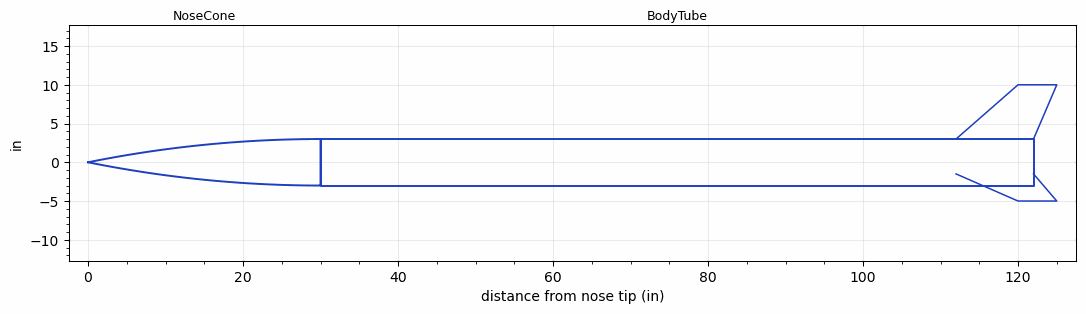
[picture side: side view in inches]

<RASAeroDocument>
 <FileVersion>2</FileVersion>
 <RocketDesign>
  <NoseCone>
   <Length>30</Length>
   <Diameter>6</Diameter>
   <Shape>Tangent Ogive</Shape>
   <Location>0</Location>
  </NoseCone>
  <BodyTube>
   <Length>92</Length>
   <Diameter>6</Diameter>
   <Location>30</Location>
   <Fin>
    <Count>3</Count>
    <Chord>10</Chord>
    <Span>7</Span>
    <SweepDistance>8</SweepDistance>
    <TipChord>5</TipChord>
    <Thickness>0.25</Thickness>
    <LERadius>0.125</LERadius>
    <Location>10</Location>
    <AirfoilSection>Double Wedge</AirfoilSection>
    <FX1>1</FX1>
    <FX3>1</FX3>
   </Fin>
  </BodyTube>
  <Surface>Smooth Paint</Surface>
  <ModifiedBarrowman>False</ModifiedBarrowman>
  <Turbulence>False</Turbulence>
  <UseBooster1>False</UseBooster1>
  <UseBooster2>False</UseBooster2>
 </RocketDesign>
 <LaunchSite>
  <Altitude>0</Altitude>
  <Pressure>0</Pressure>
  <RodAngle>0</RodAngle>
  <RodLength>4</RodLength>
  <Temperature>74</Temperature>
  <WindSpeed>0</WindSpeed>
 </LaunchSite>
 <Recovery>
  <Altitude1>1000</Altitude1>
  <Altitude2>1000</Altitude2>
  <DeviceType1>None</DeviceType1>
  <DeviceType2>None</DeviceType2>
  <Event1>False</Event1>
  <Event2>False</Event2>
  <Size1>1</Size1>
  <Size2>1</Size2>
  <EventType1>None</EventType1>
  <EventType2>None</EventType2>
  <CD1>1.33</CD1>
  <CD2>1.33</CD2>
 </Recovery>
 <SimulationList>
  <Simulation>
   <SustainerEngine>O5800  (CTI)</SustainerEngine>
   <SustainerLaunchWt>100</SustainerLaunchWt>
   <SustainerNozzleDiameter>3</SustainerNozzleDiameter>
   <SustainerCG>89</SustainerCG>
   <SustainerIgnitionDelay>0</SustainerIgnitionDelay>
   <Booster1SeparationDelay>0</Booster1SeparationDelay>
   <Booster1IgnitionDelay>0</Booster1IgnitionDelay>
   <IncludeBooster1>False</IncludeBooster1>
   <Booster2Delay>0</Booster2Delay>
   <IncludeBooster2>False</IncludeBooster2>
   <TimetoApogee>43.04878</TimetoApogee>
   <MaxAltitude>33800.3</MaxAltitude>
   <MaxVelocity>2151.055</MaxVelocity>
   <OptimumWt>65.625</OptimumWt>
   <OptimumMaxAlt>65.625</OptimumMaxAlt>
  </Simulation>
 </SimulationList>
</RASAeroDocument>
